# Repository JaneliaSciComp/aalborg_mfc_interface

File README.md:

# aalborg_mfc_interface

Authors:

    Peter Polidoro <polidorop@janelia.hhmi.org>

License:

    BSD

## More Detailed Help on Installation and Usage

[modular-devices](https://github.com/janelia-modular-devices/modular-devices)

## Device Information

```json
{
  "method":"?",
  "device_info":{
    "name":"aalborg_mfc_interface",
    "model_number":1100,
    "serial_number":0,
    "firmware_version":{
      "major":0,
      "minor":1,
      "patch":0
    }
  },
  "methods":[
    "getMemoryFree",
    "resetDefaults",
    "setSerialNumber",
    "executeStandaloneCallback",
    "getLedsPowered",
    "setMfcFlow",
    "setMfcFlows",
    "getMfcFlowSetting",
    "getMfcFlowSettings",
    "getMfcFlowMeasure",
    "getMfcFlowMeasures",
    "getAnalogInput",
    "getAnalogInputs",
    "saveState",
    "recallState",
    "getSavedStates",
    "pulseBncB"
  ],
  "status":success
}
```

## Verbose Device Information

```json
{
  "method":"??",
  "device_info":{
    "name":"aalborg_mfc_interface",
    "model_number":1100,
    "serial_number":0,
    "firmware_version":{
      "major":0,
      "minor":1,
      "patch":0
    }
  },
  "methods":[
    {
      "name":"getMemoryFree",
      "parameters":[]
    },
    {
      "name":"resetDefaults",
      "parameters":[]
    },
    {
      "name":"setSerialNumber",
      "parameters":[
        {
          "name":"serial_number",
          "type":"long",
          "min":0,
          "max":65535
        }
      ]
    },
    {
      "name":"executeStandaloneCallback",
      "parameters":[]
    },
    {
      "name":"getLedsPowered",
      "parameters":[]
    },
    {
      "name":"setMfcFlow",
      "parameters":[
        {
          "name":"mfc",
          "type":"long",
          "min":0,
          "max":2
        },
        {
          "name":"percent",
          "type":"long",
          "min":0,
          "max":100
        }
      ]
    },
    {
      "name":"setMfcFlows",
      "parameters":[
        {
          "name":"percents",
          "type":"array",
          "array_element_type":"long",
          "min":0,
          "max":100
        }
      ]
    },
    {
      "name":"getMfcFlowSetting",
      "parameters":[
        {
          "name":"mfc",
          "type":"long",
          "min":0,
          "max":2
        }
      ]
    },
    {
      "name":"getMfcFlowSettings",
      "parameters":[]
    },
    {
      "name":"getMfcFlowMeasure",
      "parameters":[
        {
          "name":"mfc",
          "type":"long",
          "min":0,
          "max":2
        }
      ]
    },
    {
      "name":"getMfcFlowMeasures",
      "parameters":[]
    },
    {
      "name":"getAnalogInput",
      "parameters":[
        {
          "name":"ain",
          "type":"long",
          "min":0,
          "max":2
        }
      ]
    },
    {
      "name":"getAnalogInputs",
      "parameters":[]
    },
    {
      "name":"saveState",
      "parameters":[
        {
          "name":"state",
          "type":"long",
          "min":0,
          "max":9
        }
      ]
    },
    {
      "name":"recallState",
      "parameters":[
        {
          "name":"state",
          "type":"long",
          "min":0,
          "max":9
        }
      ]
    },
    {
      "name":"getSavedStates",
      "parameters":[]
    },
    {
      "name":"pulseBncB",
      "parameters":[
        {
          "name":"duration",
          "units":"ms",
          "type":"long",
          "min":1,
          "max":10000
        }
      ]
    }
  ],
  "status":success
}
```

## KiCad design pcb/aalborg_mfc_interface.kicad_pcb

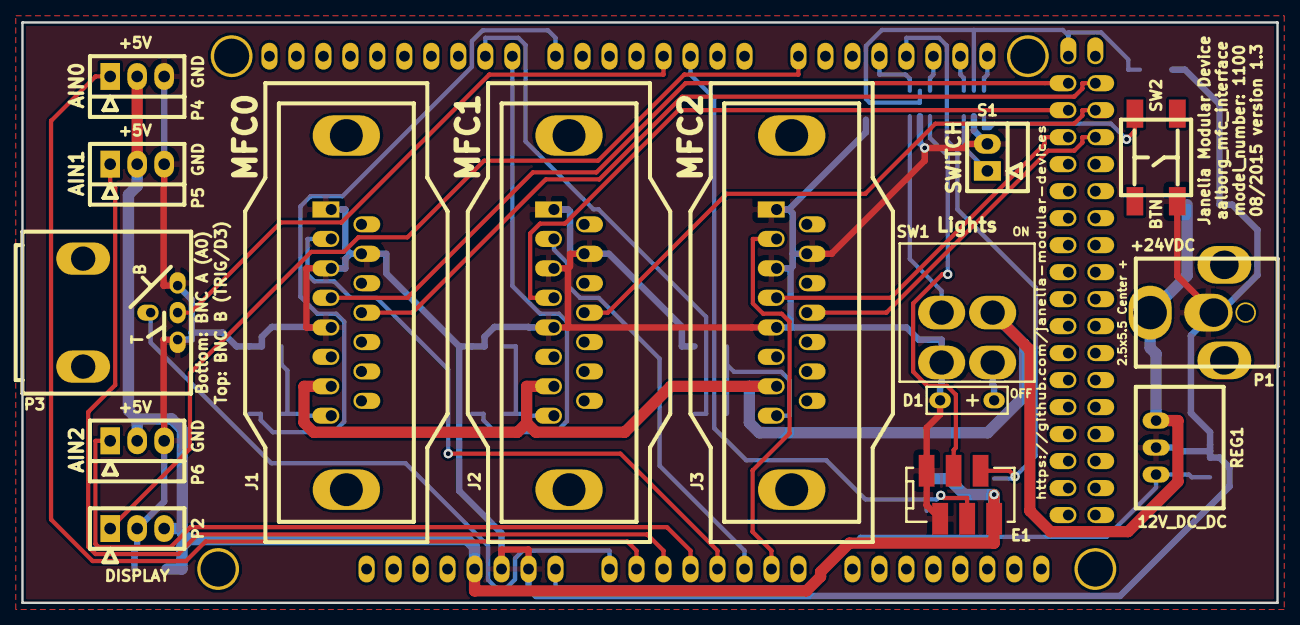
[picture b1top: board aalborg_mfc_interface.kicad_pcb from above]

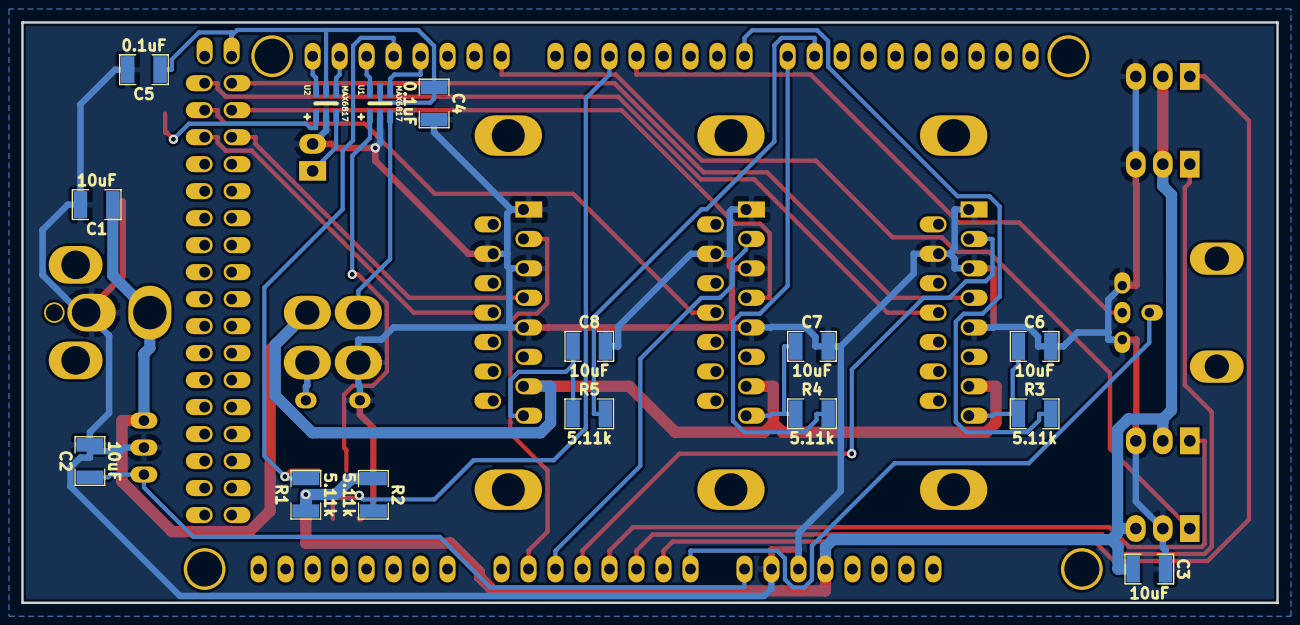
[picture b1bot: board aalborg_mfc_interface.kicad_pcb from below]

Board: 2 copper layers, 118.1 x 54.6 mm, 31 parts (15 on the bottom side), 37 nets.

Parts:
ARDUINO1: ARDUINO_MEGA; ARDUINO_MEGA_SHIELD
C1, C2, C3, C6, C7, C8: 10uF; SM1210
C4, C5: 0.1uF; SM1210
D1: LED_24V; LED_555-3XXX
E1: ENCODER_C14; Micro-MaTch_6_SMD
J1, J2, J3: DB15FV; DB15FD
P1: PWR_JACK_2.5x5.5; DCJACK_2PIN_HIGHCURRENT
P2: HEADER_01X03; Header_3_Pin
P3: BNC_DOUBLE_RA; BNC_DOUBLE
P4, P5, P6: HEADER_01X03_SHR; Header_Shrouded_3_Pin
R1, R2, R3, R4, R5: 5.11k; SM1210
REG1: CONV_DC_DC_12V_1A; DC_DC_CONV_R78C
S1: HEADER_01X02_SHR; Header_Shrouded_2_Pin
SW1: DPST_SERIES_M
SW2: KT_SWITCH
U1, U2: MAX6817

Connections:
+5V: ARDUINO1.5V_1, C3.1, E1.6, P2.3, P4.2, P5.2, P6.2, R1.1, R2.1
+5VD: ARDUINO1.5V_4, C4.1, C5.1, U1.5, U2.5
/AIN_0: ARDUINO1.A1, P4.1
/AIN_1: ARDUINO1.A2, P5.1
/AIN_2: ARDUINO1.A3, P6.1
/ANALOG_IN_0: ARDUINO1.A4, J1.2
/ANALOG_IN_1: ARDUINO1.A5, J2.2
/ANALOG_IN_2: ARDUINO1.A6, J3.2
/ANALOG_OUT_0: C6.1, J1.8, R3.1
/ANALOG_OUT_1: C7.1, J2.8, R4.1
/ANALOG_OUT_2: C8.1, J3.8, R5.1
/BNC_A: ARDUINO1.A0, P3.1
/BNC_B: ARDUINO1.3, P3.3
/BTN: SW2.2, U2.1
/D_BTN: ARDUINO1.21, U2.6
/D_ENC_BTN: ARDUINO1.19, U1.6
/D_LIGHTS: ARDUINO1.17, U1.4
/D_SWITCH: ARDUINO1.20, U2.4
/ENC_A: ARDUINO1.18, E1.5, R1.2
/ENC_B: ARDUINO1.2, E1.4, R2.2
/ENC_BTN: E1.3, U1.1
/LED_PWR: D1.1, SW1.3
/LIGHTS: SW1.5, U1.3
/PURGE_0: ARDUINO1.22, J1.4
/PURGE_1: ARDUINO1.24, J2.4
/PURGE_2: ARDUINO1.26, J3.4
/PWM_0: ARDUINO1.7, R3.2
/PWM_1: ARDUINO1.8, R4.2
/PWM_2: ARDUINO1.9, R5.2
/SWITCH: S1.1, U2.3
/TX3: ARDUINO1.14, P2.1
/VALVE_OFF_0: ARDUINO1.23, J1.12
/VALVE_OFF_1: ARDUINO1.25, J2.12
/VALVE_OFF_2: ARDUINO1.27, J3.12
/V_IN: ARDUINO1.V_IN, C2.1, REG1.3
GND: ARDUINO1.GND1, ARDUINO1.GND2, C1.2, C2.2, C3.2, C4.2, C5.2, C6.2, C7.2, C8.2, D1.2, E1.1, E1.2, J1.1, J1.3, J1.5, J1.10, J2.1, J2.3, J2.5, J2.10, J3.1, J3.3, J3.5, J3.10, P1.2, P2.2, P3.2, P3.4, P4.3, P5.3, P6.3, REG1.2, S1.2, SW1.6, SW2.3, U1.2, U2.2
VAA: C1.1, J1.7, J2.7, J3.7, P1.1, REG1.1, SW1.2

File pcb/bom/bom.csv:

Source: aalborg_mfc_interface.sch
Date: Wed 10 Dec 2014 05:16:41 PM EST

Item,Reference(s),Value,Quantity,Description,PartNumber,Vendor
1,ARDUINO1,ARDUINO_MEGA,1,1050-1018-ND,digikey
2,C1 C2 C3 C5 C6,10uF,5,445-4536-1-ND,digikey
3,C4,0.1uF,1,478-3586-1-ND,digikey
4,D1,LED_24V,1,350-1723-ND,digikey
5,E1,ENCODER_C14,1,102-1914-ND,digikey
6,J1 J2,DB15FV,2,A102054-ND,digikey
7,P1,PWR_JACK_2.5x5.5,1,CP-063BH-ND,digikey
8,P2,HEADER_01X03,1,609-3461-ND,digikey
9,R1 R2 R3 R4,5.11k,4,P5.11KAACT-ND,digikey
10,REG1,CONV_DC_DC_12V_1A,1,945-1392-5-ND,digikey
11,U1,MAX6817,1,MAX6817EUT+TCT-ND,digikey

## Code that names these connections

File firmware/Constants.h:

// ----------------------------------------------------------------------------
// Constants.h
//
//
// Authors:
// Peter Polidoro peter@polidoro.io
// ----------------------------------------------------------------------------
#ifndef CONSTANTS_H
#define CONSTANTS_H
#include "ConstantVariable.h"

namespace constants
{
enum {FRAME_COUNT=6};
enum {STATE_COUNT=10};
enum {MFC_COUNT=3};
enum {AIN_COUNT=3};

extern const unsigned int baudrate;

extern const unsigned int model_number;

extern const unsigned char firmware_major;
extern const unsigned char firmware_minor;
extern const unsigned char firmware_patch;

extern HardwareSerial & display_serial;

extern const int enc_a_pin;
extern const int enc_b_pin;
extern const int enc_btn_pin;
extern const int enc_btn_int;
extern const int btn_pin;
extern const int btn_int;
extern const int lights_pin;
extern const int bnc_b_pin;
extern const int standalone_update_period;

extern const int mfc_pwm_pins[MFC_COUNT];
extern const int mfc_ain_pins[MFC_COUNT];
extern const int mfc_purge_pins[MFC_COUNT];
extern const int mfc_valve_off_pins[MFC_COUNT];

extern const int ain_pins[AIN_COUNT];

extern const int pwm_min;
extern const int pwm_max;
extern const int ain_min;
extern const int ain_max;

extern const int percent_min;
extern const int percent_max;

extern const uint8_t states_array_default[STATE_COUNT][MFC_COUNT];

extern const uint8_t mfc_dsp_lbl_display_positions[MFC_COUNT];
extern const uint8_t ain_dsp_lbl_display_positions[AIN_COUNT];
extern const uint8_t state_dsp_lbl_display_position;
extern const uint8_t duration_dsp_lbl_display_position;

extern const uint8_t percent_display_width;

extern const uint8_t flow_var_display_positions[MFC_COUNT];
extern const uint8_t ain_dsp_var_display_positions[AIN_COUNT];
extern const uint8_t state_int_var_display_position;
extern const uint8_t duration_int_var_display_position;
extern const uint16_t duration_int_var_default;

extern const uint16_t duration_min;
extern const uint16_t duration_max;

extern ConstantString device_name;

extern ConstantString mfc_parameter_name;
extern ConstantString ain_parameter_name;
extern ConstantString percent_parameter_name;
extern ConstantString percents_parameter_name;
extern ConstantString state_parameter_name;
extern ConstantString duration_parameter_name;
extern ConstantString duration_parameter_units;

extern ConstantString execute_standalone_callback_method_name;
extern ConstantString get_leds_powered_method_name;
extern ConstantString set_mfc_flow_method_name;
extern ConstantString set_mfc_flows_method_name;
extern ConstantString get_mfc_flow_setting_method_name;
extern ConstantString get_mfc_flow_settings_method_name;
extern ConstantString get_mfc_flow_measure_method_name;
extern ConstantString get_mfc_flow_measures_method_name;
extern ConstantString get_analog_input_method_name;
extern ConstantString get_analog_inputs_method_name;
extern ConstantString save_state_method_name;
extern ConstantString recall_state_method_name;
extern ConstantString get_saved_states_method_name;
extern ConstantString pulse_bnc_b_method_name;

extern ConstantString states_name;
extern ConstantString frame0_name;
extern ConstantString frame1_name;
extern ConstantString frame2_name;
extern const ConstantString frame_name_array[FRAME_COUNT];
extern ConstantString mfc0_dsp_lbl_string;
extern ConstantString mfc1_dsp_lbl_string;
extern ConstantString mfc2_dsp_lbl_string;
extern const ConstantString mfc_dsp_lbl_strings[MFC_COUNT];
extern ConstantString ain0_dsp_lbl_string;
extern ConstantString ain1_dsp_lbl_string;
extern ConstantString ain2_dsp_lbl_string;
extern const ConstantString ain_dsp_lbl_strings[AIN_COUNT];
}
#endif

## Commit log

2014-11-21 Initial commit.
2014-11-25 Setup pcb schematic.
2014-11-25 Updated component library reference.
2014-12-01 Added some schematic components.
2014-12-04 Initial board layout.
2014-12-05 Initial pcb layout.
2014-12-08 Finished pcb version 1.0.
2014-12-10 Initial version 1.1 design.
2014-12-10 Added digikey_order.txt.
2014-12-11 Added some items to the bom.
2014-12-11 Added bom.csv.
2014-12-11 Removed header and renamed bom.
2014-12-11 Fixed missing Description field.
2014-12-11 Updated line terminator to work on Windows as well.
2014-12-11 Moved additional parts to new bom.
2014-12-11 Removed extra symbols.
2014-12-11 Cleaned up component descriptions.
2014-12-11 Updated descriptions.
2014-12-11 Added order csv files.
2014-12-11 Use automatically generated vendor order csv files.
2014-12-11 Removed external library references.
2014-12-12 Updated ENCODER_C14.
2015-01-05 Put model_number back on pcb silk screen.
2015-01-08 Updated design with changes first made to power_switch_controller.
2015-01-12 Initial firmware commit.
2015-01-13 Incremental changes towards version 1.1.
2015-01-14 Progress on pcb 1.1 design and firmware 1.0.
2015-01-15 Fixed comment error.
2015-01-16 Progress towards pcb v1.1.
2015-01-20 Finished pcb v1.1.
2015-01-20 Added schematic documentation files.
2015-01-20 Minor changes to names.
2015-01-28 remote -> modular.
2015-01-28 Updated repository link.
2015-02-17 Initial changes to update to new organization scheme.
2015-02-18 Added initial StandaloneInterface code.
2015-02-19 Assembled DisplayElements into arrays.
2015-02-19 Added StandaloneInterface frames and callback functions.
2015-02-19 Intermittent changes.
2015-02-21 Added methods.
2015-02-23 Added StandAlone frames.
2015-02-23 Finished pcb v1.2.
2015-02-25 Modified display and interactive variables.
2015-03-19 StandardCplusplus -> Array. Updated pin constants.
2015-03-19 Made display_serial a reference.
2015-03-24 Use new libraries ConstantVariable and SavedVariable.
2015-03-27 Added images.
2015-04-21 setFlashString -> setConstantString.
2015-04-21 Updated README.
2015-04-24 Added LICENSE.
2015-06-23 Added pulseBncB method.
2015-07-13 JaneliaSciComp -> janelia-modular-devices.
2015-07-24 Updated author/license.
2015-07-24 Updated documentation.
2015-07-24 Modified documentation.
2015-07-24 Moved README information to top level README.
2015-07-28 boolean -> bool.
2015-08-10 Tiny changes to create v1.3.
2015-08-10 SPST switch -> DPST switch.
2015-08-10 Updated digikey_order_pcb_add.
2015-09-09 led_pwr_pin -> lights_pin.
2015-10-16 Added GenericSerial.
2015-10-30 Upgraded to use new versions of ModularDevice and StandaloneInterface.
2016-09-19 Updated some pointer and reference spacing.
2016-09-21 pcb -> hardware.
2018-04-12 *.md -> *.org.
2018-08-12 polidorop@janelia.hhmi.org -> peterpolidoro@gmail.com
2018-08-27 Combined software and hardware licenses.
2021-09-17 Update email address
